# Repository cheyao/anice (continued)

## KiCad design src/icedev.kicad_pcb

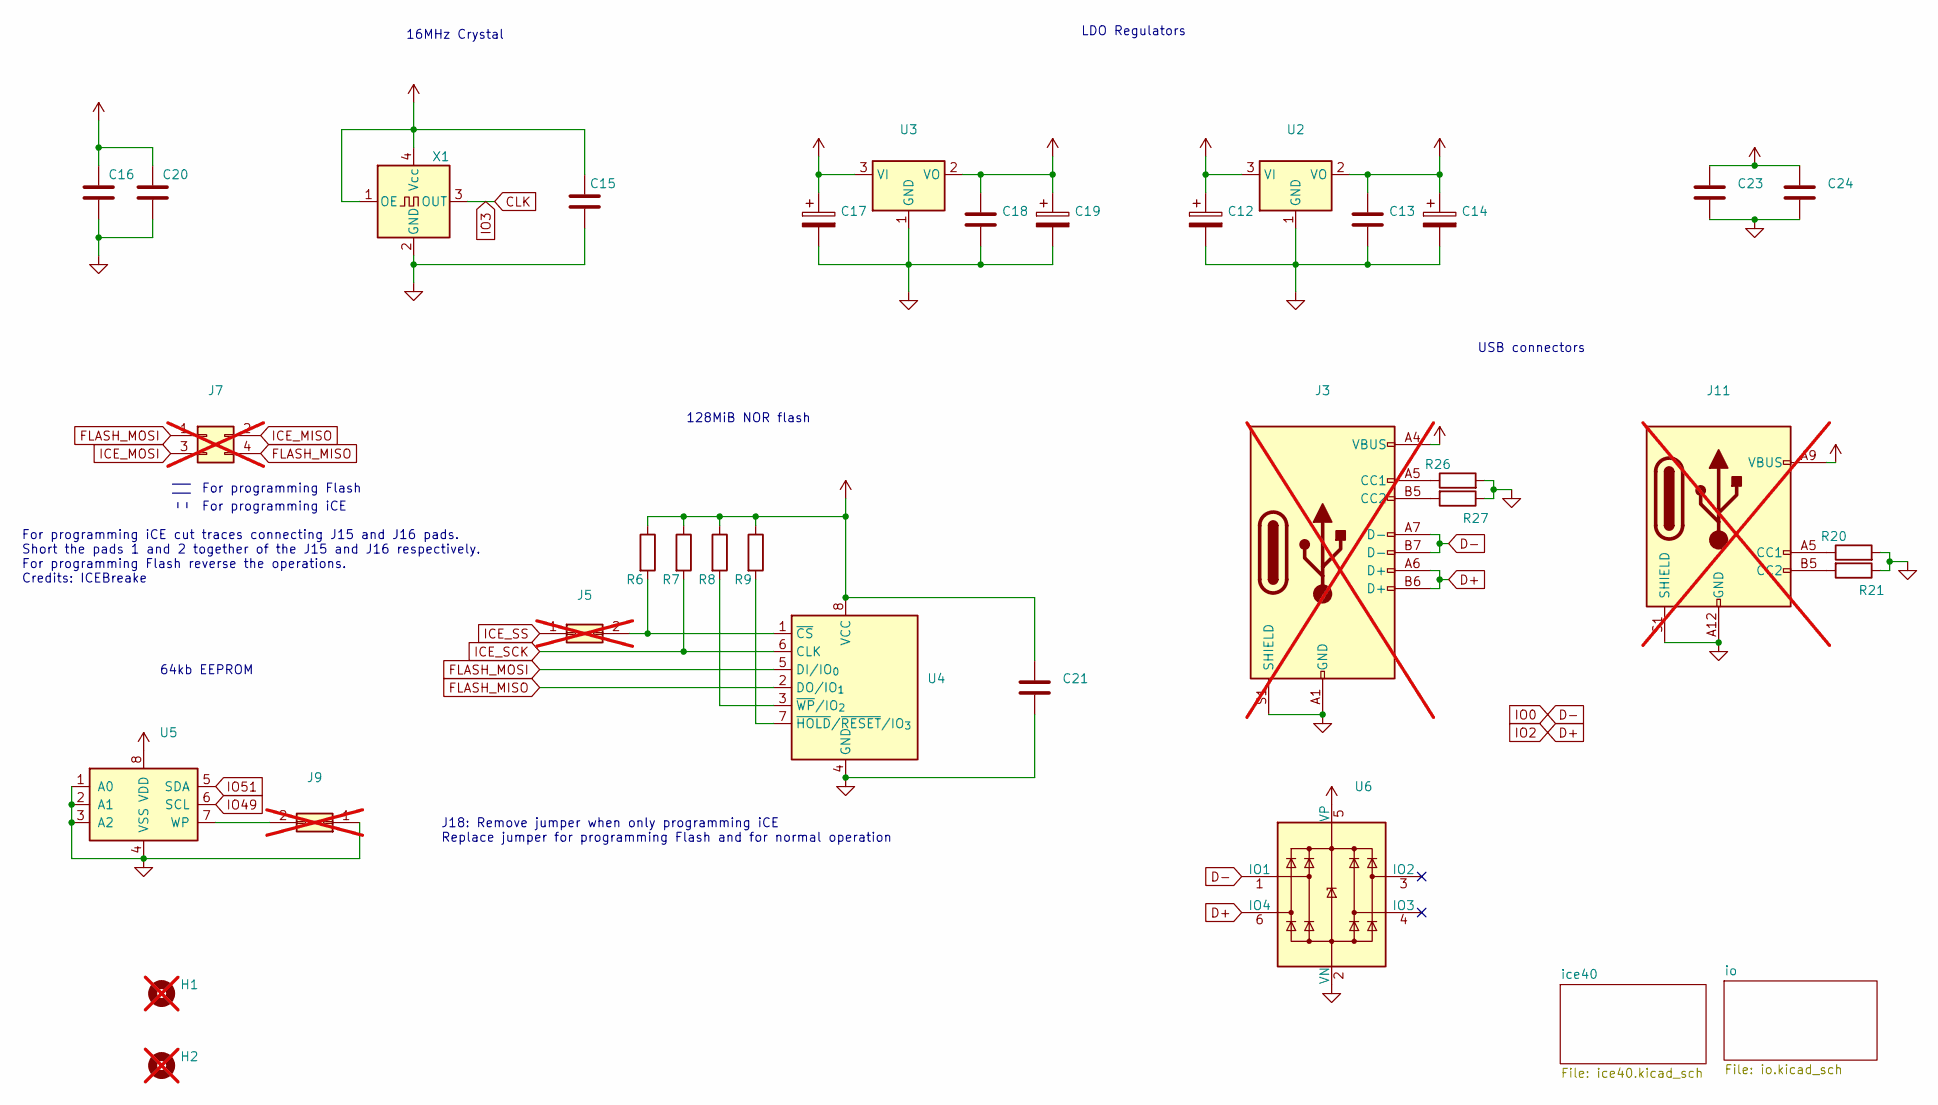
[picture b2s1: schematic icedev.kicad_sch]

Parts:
C12, C14, C17, C19: 10u; C_0402_1005Metric; JLCPCB Part # C15525
C13, C15, C16, C18, C21, C23, C24: 0.1u; C_0402_1005Metric; JLCPCB Part # C1525
C20: 10n; C_0402_1005Metric; JLCPCB Part # C15195
H1, H2: MountingHole; MountingHole_2.2mm_M2; not fitted
J3: USB_C_Receptacle_USB2.0_14P; USB_C_Receptacle_GCT_USB4105-xx-A_16P_TopMnt_Horizontal; not fitted
J5, J9: Conn_02x01; PinHeader_2x01_P2.54mm_Vertical; not fitted
J7: Conn_02x02_Odd_Even; PinSocket_2x02_P2.54mm_Vertical; not fitted
J11: USB_C_Receptacle_PowerOnly_6P; USB_C_Receptacle_GCT_USB4135-GF-A_6P_TopMnt_Horizontal; not fitted
R6, R7, R8, R9: 10K; R_0805_2012Metric; JLCPCB Part # C17414
R20, R21: 5.1K; R_0402_1005Metric; JLCPCB Part # C25905
R26, R27: 5.1K; R_0805_2012Metric; JLCPCB Part # C27834
U2: AMS1117-1.2; SOT-223-3_TabPin2; JLCPCB Part # C14529
U3: AMS1117-3.3; SOT-223-3_TabPin2; JLCPCB Part # C6186
U4: W25Q128JVS; SOIC-8_5.3x5.3mm_P1.27mm; JLCPCB Part # C97521
U5: FM24C64B; SOIC-8_3.9x4.9mm_P1.27mm; JLCPCB Part # C79988
U6: SRV05-4; SOT-23-6-routable; JLCPCB Part # C85364
X1: MPUOSC; Oscillator_SMD_Abracon_ASE-4Pin_3.2x2.5mm; JLCPCB Part # C13738

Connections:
+1V2: C13.1, C14.1, C16.1, C20.1, U2.2 (VO); also elsewhere on the board
+3V3: C12.1, C15.1, C18.1, C19.1, C21.1, R6.1, R7.1, R8.1, R9.1, U2.3 (VI), U3.2 (VO), U4.8 (VCC), U5.8 (VDD), X1.1 (OE), X1.4 (Vcc); also elsewhere on the board
+5V: C17.1, C23.1, C24.1, J3.A4 (VBUS), J3.A9 (VBUS), J3.B4 (VBUS), J3.B9 (VBUS), J11.A9 (VBUS), J11.B9 (VBUS), U3.3 (VI), U6.5 (VP); also elsewhere on the board
CLK: X1.3 (OUT); also elsewhere on the board
D+: J3.A6 (D+), J3.B6 (D+), U6.6 (IO4); also elsewhere on the board
D-: J3.A7 (D-), J3.B7 (D-), U6.1 (IO1); also elsewhere on the board
FLASH_MISO: J7.4, U4.2 (DO/IO_{1}); also elsewhere on the board
FLASH_MOSI: J7.1, U4.5 (DI/IO_{0}); also elsewhere on the board
GND: C12.2, C13.2, C14.2, C15.2, C16.2, C17.2, C18.2, C19.2, C20.2, C21.2, C23.2, C24.2, J3.A1 (GND), J3.A12 (GND), J3.B1 (GND), J3.B12 (GND), J3.S1 (SHIELD), J9.1, J11.A12 (GND), J11.B12 (GND), J11.S1 (SHIELD), R20.2, R21.1, R26.2, R27.1, U2.1 (GND), U3.1 (GND), U4.4 (GND), U5.1 (A0), U5.2 (A1), U5.3 (A2), U5.4 (VSS), U6.2 (VN), X1.2 (GND); also elsewhere on the board
ICE_MISO: J7.2; also elsewhere on the board
ICE_MOSI: J7.3; also elsewhere on the board
ICE_SCK: R7.2, U4.6 (CLK); also elsewhere on the board
ICE_SS: J5.1; also elsewhere on the board
IO49: U5.6 (SCL); also elsewhere on the board
IO51: U5.5 (SDA); also elsewhere on the board
unnamed: J3.A5 (CC1), R26.1
unnamed: J3.B5 (CC2), R27.2
unnamed: J5.2, R6.2, U4.1 (~CS)
unnamed: J9.2, U5.7 (WP)
unnamed: J11.A5 (CC1), R20.1
unnamed: J11.B5 (CC2), R21.2
unnamed: R9.2, U4.7 (~HOLD/~RESET/IO_{3})
unnamed: R8.2, U4.3 (~WP/IO_{2})

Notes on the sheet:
For programming Flash
J18: Remove jumper when only programming iCE Replace jumper for programming Flash and for normal operation
64kb EEPROM
16MHz Crystal
USB connectors
For programming iCE cut traces connecting J15 and J16 pads. Short the pads 1 and 2 together of the J15 and J16 respectively. For programming Flash reverse the operations. Credits: ICEBreake
128MiB NOR flash
LDO Regulators
For programming iCE

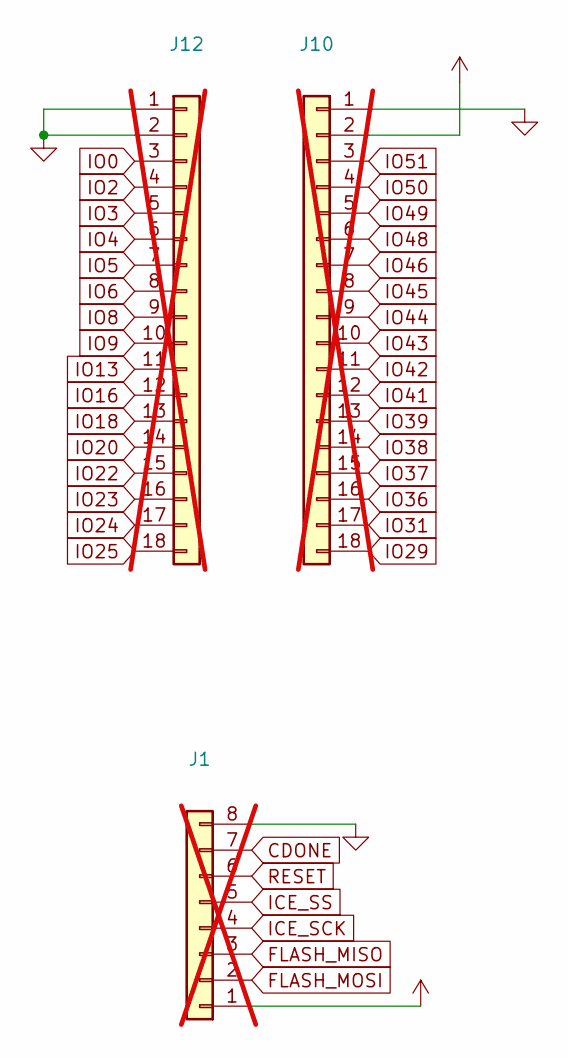
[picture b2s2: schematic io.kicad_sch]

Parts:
J1: Conn_01x08; PinSocket_1x08_P2.54mm_Vertical; not fitted
J10, J12: Conn_01x18; PinSocket_1x18_P2.54mm_Vertical; not fitted

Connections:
+5V: J1.1, J10.2; also elsewhere on the board
CDONE: J1.7; also elsewhere on the board
CLK: J12.5; also elsewhere on the board
D+: J12.4; also elsewhere on the board
D-: J12.3; also elsewhere on the board
FLASH_MISO: J1.3; also elsewhere on the board
FLASH_MOSI: J1.2; also elsewhere on the board
GND: J1.8, J10.1, J12.1, J12.2; also elsewhere on the board
ICE_SCK: J1.4; also elsewhere on the board
ICE_SS: J1.5; also elsewhere on the board
IO4: J12.6; also elsewhere on the board
IO5: J12.7; also elsewhere on the board
IO6: J12.8; also elsewhere on the board
IO8: J12.9; also elsewhere on the board
IO9: J12.10; also elsewhere on the board
IO13: J12.11; also elsewhere on the board
IO16: J12.12; also elsewhere on the board
IO18: J12.13; also elsewhere on the board
IO20: J12.14; also elsewhere on the board
IO22: J12.15; also elsewhere on the board
IO23: J12.16; also elsewhere on the board
IO24: J12.17; also elsewhere on the board
IO25: J12.18; also elsewhere on the board
IO29: J10.18; also elsewhere on the board
IO31: J10.17; also elsewhere on the board
IO36: J10.16; also elsewhere on the board
IO37: J10.15; also elsewhere on the board
IO38: J10.14; also elsewhere on the board
IO39: J10.13; also elsewhere on the board
IO41: J10.12; also elsewhere on the board
IO42: J10.11; also elsewhere on the board
IO43: J10.10; also elsewhere on the board
IO44: J10.9; also elsewhere on the board
IO45: J10.8; also elsewhere on the board
IO46: J10.7; also elsewhere on the board
IO48: J10.6; also elsewhere on the board
IO49: J10.5; also elsewhere on the board
IO50: J10.4; also elsewhere on the board
IO51: J10.3; also elsewhere on the board
RESET: J1.6; also elsewhere on the board

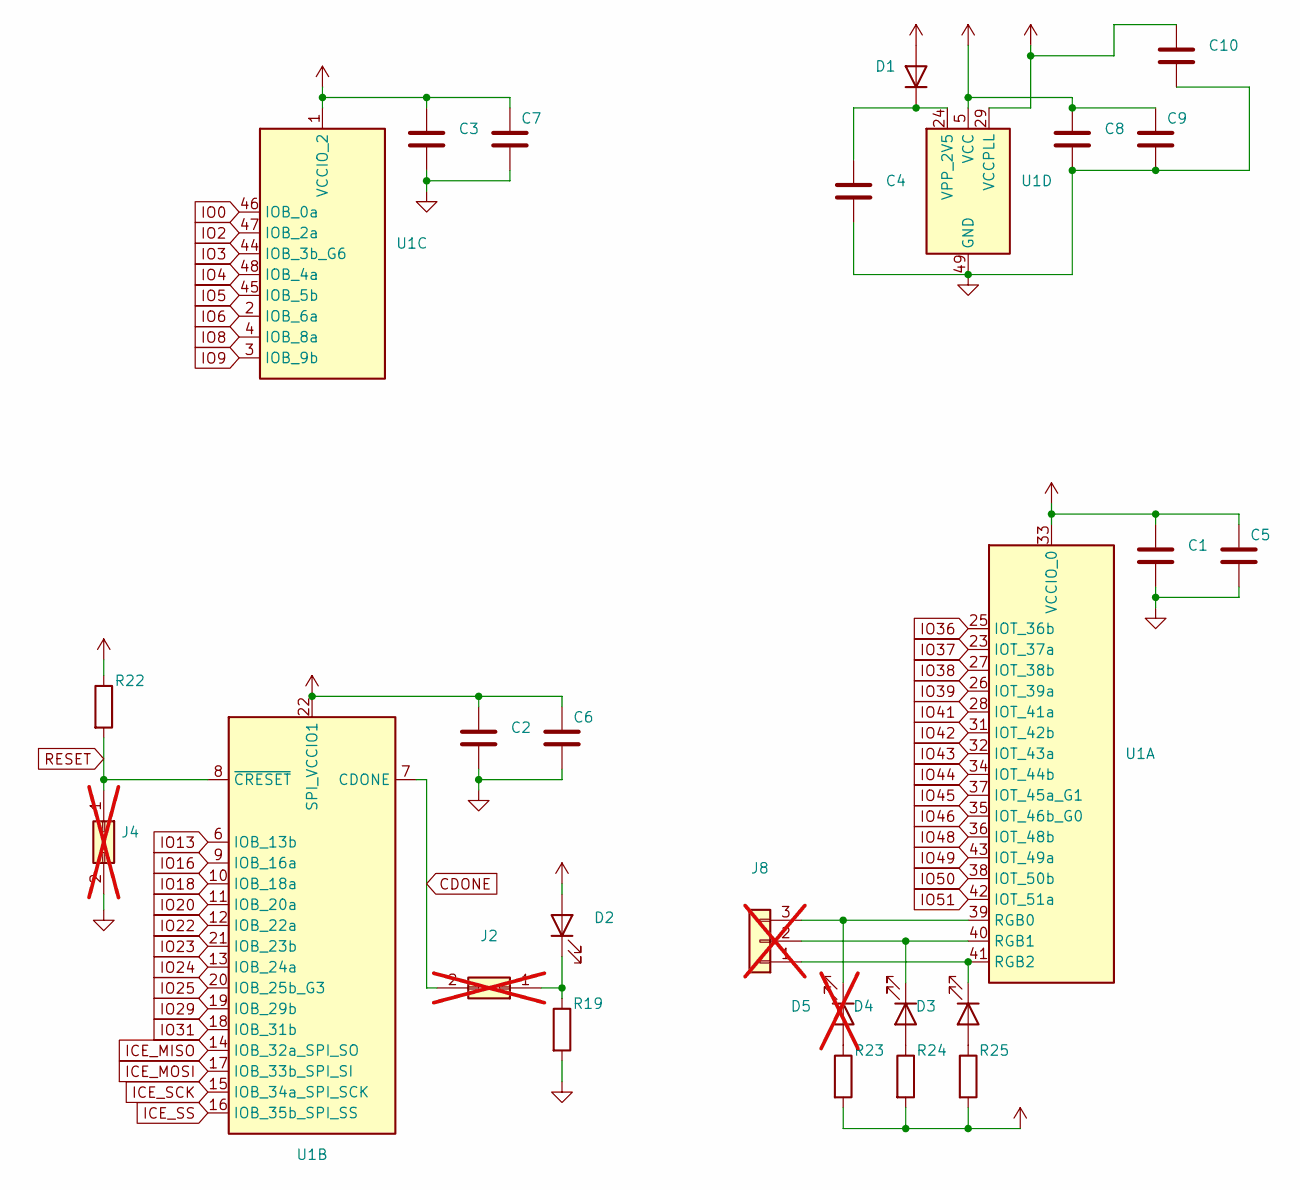
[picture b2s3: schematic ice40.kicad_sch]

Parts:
C1, C2, C3, C4, C8, C10: 0.1u; C_0402_1005Metric; JLCPCB Part # C1525
C5, C6, C7, C9: 10n; C_0402_1005Metric; JLCPCB Part # C15195
D1: Schottky Diode; D_SOD-123; JLCPCB Part # C8598
D2, D4: G; LED_0805_2012Metric; JLCPCB Part # C2297
D3: R; LED_0603_1608Metric; JLCPCB Part # C2286
D5: B; LED_0201_0603Metric_Pad0.64x0.40mm_HandSolder; not fitted
J2, J4: Conn_02x01; PinHeader_2x01_P2.54mm_Vertical; not fitted
J8: Conn_01x03; PinHeader_1x03_P2.54mm_Vertical; not fitted
R19, R22, R23, R24, R25: 1K; R_0805_2012Metric; JLCPCB Part # C17513
U1: ICE40UP5K-SG48ITR; QFN-48-1EP_7x7mm_P0.5mm_EP5.6x5.6mm; JLCPCB Part # C2678152

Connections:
+1V2: C8.1, C9.1, C10.1, U1.5 (VCC), U1.29 (VCCPLL), U1.30 (VCC); also elsewhere on the board
+3V3: C1.1, C2.1, C3.1, C5.1, C6.1, C7.1, D1.2 (A), D2.2 (A), R22.1, R23.2, R24.2, R25.2, U1.1 (VCCIO_2), U1.22 (SPI_VCCIO1), U1.33 (VCCIO_0); also elsewhere on the board
CDONE: J2.2, U1.7 (CDONE); also elsewhere on the board
CLK: U1.44 (IOB_3b_G6); also elsewhere on the board
D+: U1.47 (IOB_2a); also elsewhere on the board
D-: U1.46 (IOB_0a); also elsewhere on the board
GND: C1.2, C2.2, C3.2, C4.2, C5.2, C6.2, C7.2, C8.2, C9.2, C10.2, J4.2, R19.2, U1.49 (GND); also elsewhere on the board
ICE_MISO: U1.14 (IOB_32a_SPI_SO); also elsewhere on the board
ICE_MOSI: U1.17 (IOB_33b_SPI_SI); also elsewhere on the board
ICE_SCK: U1.15 (IOB_34a_SPI_SCK); also elsewhere on the board
ICE_SS: U1.16 (IOB_35b_SPI_SS); also elsewhere on the board
IO4: U1.48 (IOB_4a); also elsewhere on the board
IO5: U1.45 (IOB_5b); also elsewhere on the board
IO6: U1.2 (IOB_6a); also elsewhere on the board
IO8: U1.4 (IOB_8a); also elsewhere on the board
IO9: U1.3 (IOB_9b); also elsewhere on the board
IO13: U1.6 (IOB_13b); also elsewhere on the board
IO16: U1.9 (IOB_16a); also elsewhere on the board
IO18: U1.10 (IOB_18a); also elsewhere on the board
IO20: U1.11 (IOB_20a); also elsewhere on the board
IO22: U1.12 (IOB_22a); also elsewhere on the board
IO23: U1.21 (IOB_23b); also elsewhere on the board
IO24: U1.13 (IOB_24a); also elsewhere on the board
IO25: U1.20 (IOB_25b_G3); also elsewhere on the board
IO29: U1.19 (IOB_29b); also elsewhere on the board
IO31: U1.18 (IOB_31b); also elsewhere on the board
IO36: U1.25 (IOT_36b); also elsewhere on the board
IO37: U1.23 (IOT_37a); also elsewhere on the board
IO38: U1.27 (IOT_38b); also elsewhere on the board
IO39: U1.26 (IOT_39a); also elsewhere on the board
IO41: U1.28 (IOT_41a); also elsewhere on the board
IO42: U1.31 (IOT_42b); also elsewhere on the board
IO43: U1.32 (IOT_43a); also elsewhere on the board
IO44: U1.34 (IOT_44b); also elsewhere on the board
IO45: U1.37 (IOT_45a_G1); also elsewhere on the board
IO46: U1.35 (IOT_46b_G0); also elsewhere on the board
IO48: U1.36 (IOT_48b); also elsewhere on the board
IO49: U1.43 (IOT_49a); also elsewhere on the board
IO50: U1.38 (IOT_50b); also elsewhere on the board
IO51: U1.42 (IOT_51a); also elsewhere on the board
unnamed: C4.1, D1.1 (K), U1.24 (VPP_2V5)
unnamed: D2.1 (K), J2.1, R19.1
unnamed: D3.2 (A), R25.1
unnamed: D3.1 (K), J8.1, U1.41 (RGB2)
unnamed: D4.2 (A), R24.1
unnamed: D4.1 (K), J8.2, U1.40 (RGB1)
unnamed: D5.2 (A), R23.1
unnamed: D5.1 (K), J8.3, U1.39 (RGB0)
RESET: J4.1, R22.2, U1.8 (~CRESET); also elsewhere on the board

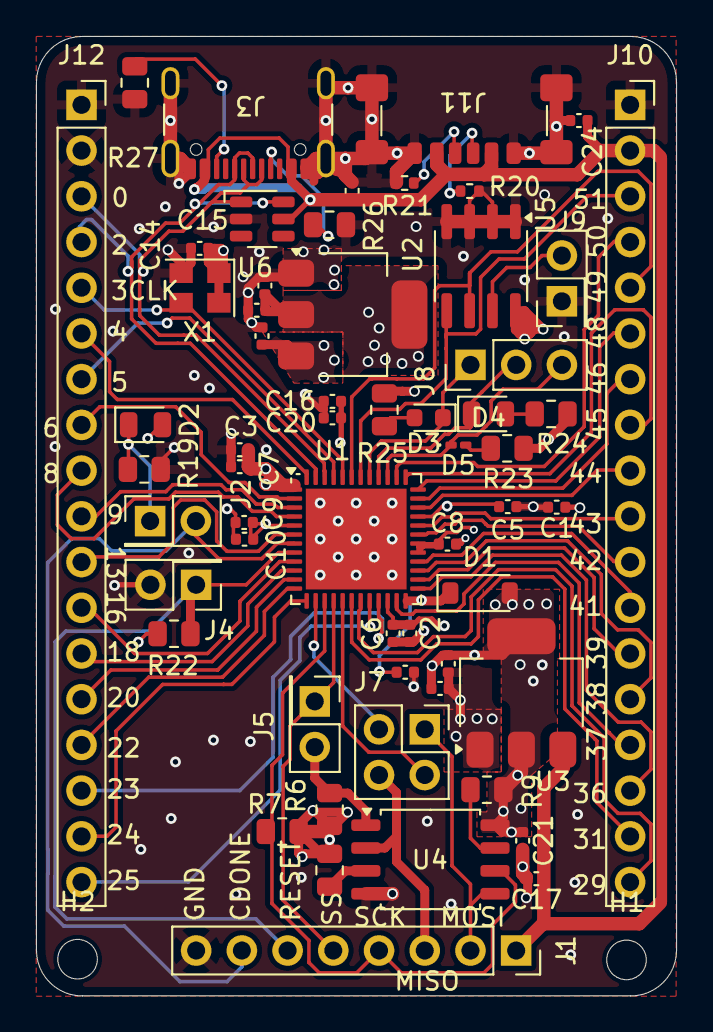
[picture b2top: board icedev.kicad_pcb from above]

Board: 4 copper layers, 35.6 x 53.3 mm, 60 parts (0 on the bottom side), 60 nets.

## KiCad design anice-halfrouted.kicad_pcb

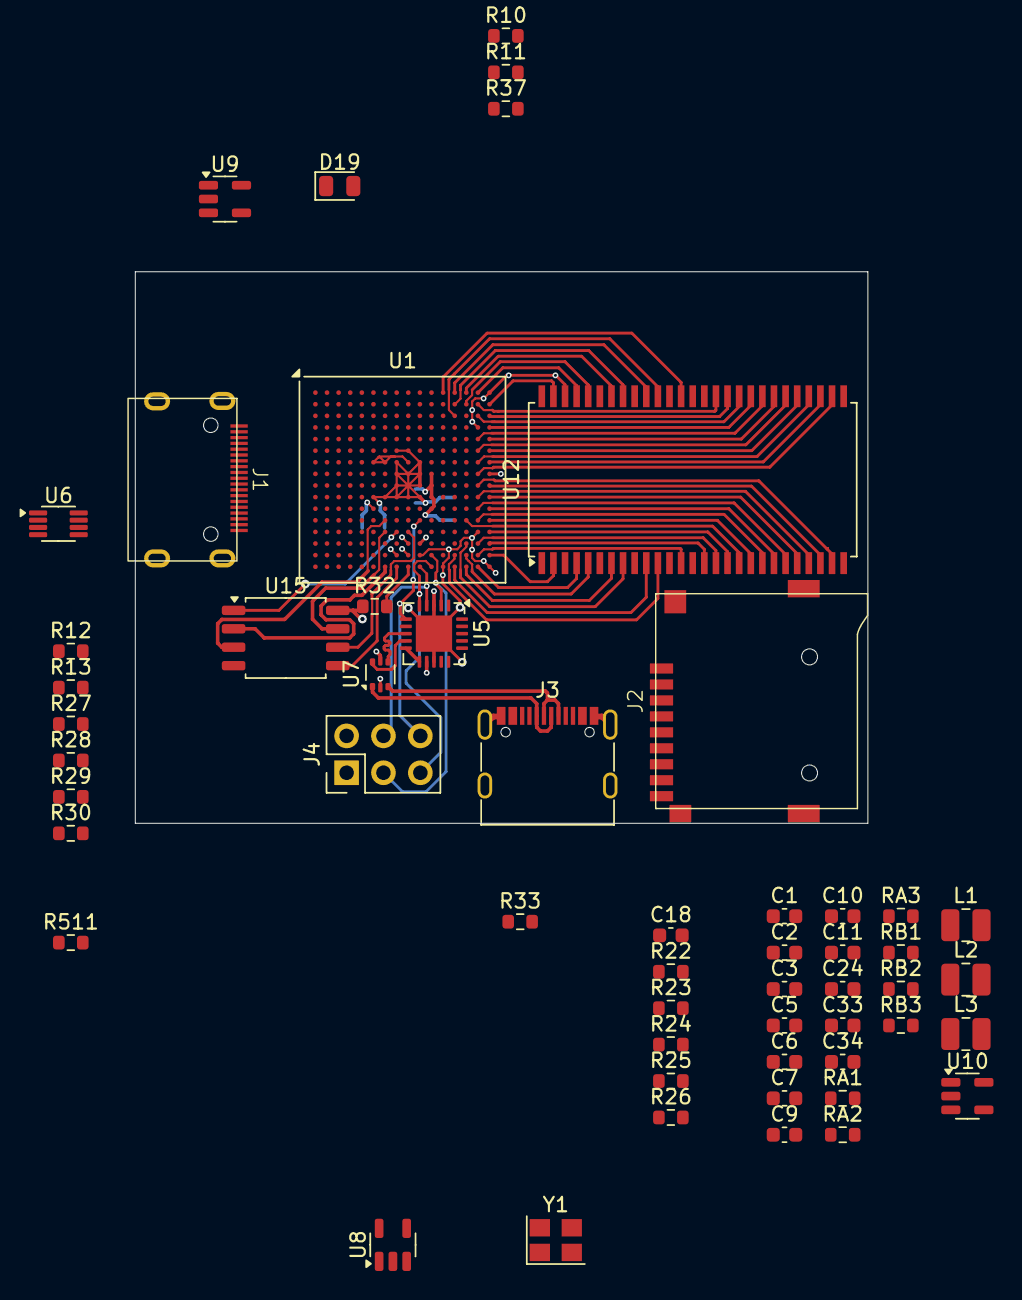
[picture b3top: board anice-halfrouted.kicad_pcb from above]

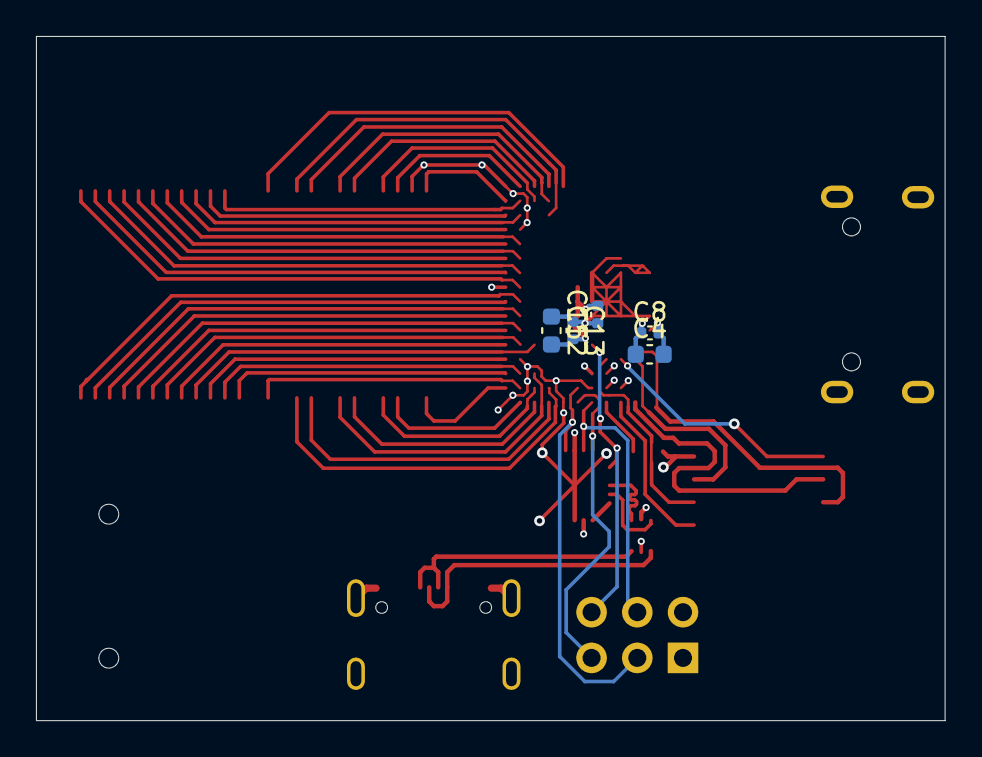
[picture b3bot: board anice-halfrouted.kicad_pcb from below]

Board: 4 copper layers, 50.5 x 38.0 mm, 59 parts (5 on the bottom side), 77 nets.

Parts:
C1, C3, C5, C7, C9, C11: 22uF; C_0603_1608Metric
C2, C4, C12: 10uF; C_0603_1608Metric
C6, C10, C18: 100pF; C_0603_1608Metric
C8, C13, C15: 100nF; C_0402_1005Metric
C24, C33, C34: 2.2uF; C_0603_1608Metric
D19: RED; LED_0805_2012Metric
J1: HDMI_C_1.3; XKB Connection A71-05H4-111N1
J2: Micro_SD_Card_Det1; XYECONN TF-015-ZYD9AH1.85
J3: USB_C_Receptacle_USB2.0_14P; USB_C_Receptacle_G-Switch_GT-USB-7010ASV
J4: CONN_02X03; PinHeader_2x03_P2.54mm_Vertical
L1, L2, L3: 2.2uH; L_1008_2520Metric
R10, R11: 5.1k; R_0603_1608Metric
R12, R13, R27, R28: 10k; R_0603_1608Metric
R22, R23: 3.3k; R_0603_1608Metric
R24: 100k; R_0603_1608Metric
R25, R26, R30, R32, R33, R511: 4.7k; R_0603_1608Metric
R29: 1k; R_0603_1608Metric
R37: 549; R_0603_1608Metric
RA1, RA2, RA3: 15k; R_0603_1608Metric
RB1: 18k; R_0603_1608Metric
RB2: 4.7k; R_0603_1608Metric
RB3: 3.3k; R_0603_1608Metric
U1: ECP5U_12_CABGA256; BGA-256_14.0x14.0mm_Layout16x16_P0.8mm_Ball0.45mm_Pad0.32mm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
U5: FT231XQ; QFN-20-1EP_4x4mm_P0.5mm_EP2.5x2.5mm
U6: PCA9306DC1; VSSOP-8_2.3x2mm_P0.5mm
U7: USBLC6-2P6; SOT-666
U8, U9, U10: TLV62569DBV; SOT-23-5
U12: W9825G6KH-6; TSOP-II-54_22.2x10.16mm_P0.8mm
U15: W25Q128JVS; SOIC-8_5.3x5.3mm_P1.27mm
Y1: ECS-2520MV-xxx-xx; Crystal_SMD_3225-4Pin_3.2x2.5mm

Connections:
+1V1: C2.1, C3.1, C34.1, L1.2, RA1.1, U1.G6 (VCC[6]), U1.G7 (VCC[6]), U1.G9 (VCC[6]), U1.L8 (VCC[6]), U1.L9 (VCC[6]), U1.L10 (VCC[6])
+2V5: C10.1, C11.1, C33.1, L2.2, R22.1, R23.1, RA2.1, U1.G11 (VCCAUX[2]), U1.L7 (VCCAUX[2]), U6.2 (VREF1)
+3V3: C4.2, C6.1, C7.1, C8.2, C12.2, C13.2, C15.2, C24.1, J4.2, L3.2, R12.1, R13.1, R27.1, R28.1, R29.1, R30.1, R32.1, R33.1, R511.1, RA3.1, U1.F6 (VCCIO0[2]), U1.F7 (VCCIO0[2]), U1.F10 (VCCIO1[2]), U1.F11 (VCCIO1[2]), U1.H6 (VCCIO7[2]), U1.H7 (VCCIO7[2]), U1.H11 (VCCIO2[2]), U1.J6 (VCCIO6[2]), U1.J7 (VCCIO6[2]), U1.J11 (VCCIO2[2]), U1.K11 (VCCIO3[2]), U1.L6 (VCCIO8), U1.L11 (VCCIO3[2]), U1.P10 (CFG_1), U1.R8 (PB13A/+/SN/CSN), U6.8 (EN), U12.1 (VDD), U12.3 (VDDQ), U12.9 (VDDQ), U12.14 (VDD), U12.27 (VDD), U12.43 (VDDQ), U12.49 (VDDQ), U15.8 (VCC)
+5V: C1.1, C5.1, C9.1, J1.18 (+5V), J3.A4 (VBUS), J3.A9 (VBUS), J3.B4 (VBUS), J3.B9 (VBUS), R24.1, R25.1, R26.1, U5.12 (VCC), U7.5 (VBUS), U8.1 (EN), U8.4 (VIN), U9.1 (EN), U9.4 (VIN), U10.1 (EN), U10.4 (VIN)
/Power/FB1: C2.2, RA1.2, RB1.2, U8.5 (FB)
/Power/FB2: C10.2, RA2.2, RB2.2, U9.5 (FB)
/Power/FB3: C6.2, RA3.2, RB3.2, U10.5 (FB)
/Power/L1: L1.1, U8.3 (SW)
/Power/L2: L2.1, U9.3 (SW)
/Power/L3: L3.1, U10.3 (SW)
/USB/LED_TXLED: D19.1 (K), R37.2
CLK: R29.2, U1.N9 (CCLK/MCLK/SCK), U15.6 (CLK)
DONE: R33.2, U1.P9 (DONE)
FPDI_SCL: R23.2, U6.3 (SCL1)
FPDI_SDA: R22.2, U6.4 (SDA1)
FT2V5: D19.2 (A), U5.10 (3V3OUT), U5.11 (~RESET), U5.20 (VCCIO)
FTDI_nTXLED: R37.1, U5.7 (CBUS2)
GND: C1.2, C3.2, C4.1, C5.2, C7.2, C8.1, C9.2, C11.2, C12.1, C13.1, C15.1, C18.2, C24.2, C33.2, C34.2, J1.1 (D2S), J1.4 (D1S), J1.7 (D0S), J1.10 (CKS), J1.13 (GND), J1.SH, J3.A1 (GND), J3.A12 (GND), J3.B1 (GND), J3.B12 (GND), J3.S1 (SHIELD), J4.1, R10.1, R11.1, RB1.1, RB2.1, RB3.1, U1.A1 (GND[27]), U1.A16 (GND[27]), U1.D2 (GND[27]), U1.D15 (GND[27]), U1.F8 (GND[27]), U1.F9 (GND[27]), U1.G8 (GND[27]), U1.G10 (GND[27]), U1.H1 (GND[27]), U1.H8 (GND[27]), U1.H9 (GND[27]), U1.H10 (GND[27]), U1.H16 (GND[27]), U1.J8 (GND[27]), U1.J9 (GND[27]), U1.J10 (GND[27]), U1.K6 (GND[27]), U1.K7 (GND[27]), U1.K8 (GND[27]), U1.K9 (GND[27]), U1.K10 (GND[27]), U1.N2 (GND[27]), U1.N10 (CFG_0), U1.N15 (GND[27]), U1.R10 (CFG_2), U1.T1 (GND[27]), U1.T5 (GND[27]), U1.T12 (GND[27]), U1.T16 (GND[27]), U5.3 (GND), U5.13 (GND), U5.21 (GND), U6.1 (GND), U7.2 (GND), U8.2 (GND), U9.2 (GND), U10.2 (GND), U12.6 (VSSQ), U12.12 (VSSQ), U12.28 (VSS), U12.41 (VSS), U12.46 (VSSQ), U12.52 (VSSQ), U12.54 (VSS), U15.4 (GND)
GPDI_SCL: J1.15 (SCL), R25.2, U6.6 (SCL2)
GPDI_SDA: J1.16 (SDA), R26.2, U6.5 (SDA2)
INITN: R32.2, U1.T9 (INITN)
IO0: R28.2, U1.T8 (PB11B/-/D0/MOSI/IO0), U15.5 (DI/IO_{0})
IO1: R27.2, U1.T7 (PB11A/+/D1/MISO/IO1), U15.2 (DO/IO_{1})
IO2: R13.2, U1.M7 (PB9B/-/D2/IO2), U15.3 (~WP/IO_{2})
IO3: R12.2, U1.N7 (PB9A/+/D3/IO3), U15.7 (~HOLD/~RESET/IO_{3})
JTAG_TCK: J4.4, U1.T10 (TCK), U5.4 (~DSR)
JTAG_TDI: J4.3, U1.R11 (TDI), U5.2 (~RI)
JTAG_TDO: J4.6, U1.M10 (TDO), U5.6 (~CTS)
JTAG_TMS: J4.5, U1.T11 (TMS), U5.5 (~DCD)
unnamed: J3.A5 (CC1), R11.2
unnamed: J3.B5 (CC2), R10.2
unnamed: J3.A6 (D+), J3.B6 (D+), U7.3 (IO2)
unnamed: J3.A7 (D-), J3.B7 (D-), U7.1 (IO1)
unnamed: R511.2, U1.R9 (PROGRAMN)
unnamed: U5.9 (USBDM), U7.6 (IO1)
unnamed: U5.8 (USBDP), U7.4 (IO2)
unnamed: C18.1, R24.2, U6.7 (VREF2)
SDRAM_A0: U1.K16 (PR23C/+/PCLKT2_0/RDQ20), U12.23 (A0)
SDRAM_A1: U1.K15 (PR23D/-/PCLKC2_0/RDQ20), U12.24 (A1)
SDRAM_A2: U1.J16 (PR23A/+/PCLKT2_1/HS/RDQ20), U12.25 (A2)
SDRAM_A3: U1.J15 (PR23B/-/PCLKC2_1/HS/RDQ20), U12.26 (A3)
SDRAM_A4: U1.H15 (PR20B/-/HS/RDQSN20), U12.29 (A4)
SDRAM_A5: U1.G16 (PR20A/+/GR_PCLK2_1/HS/RDQS20), U12.30 (A5)
SDRAM_A6: U1.G15 (PR14B/-/HS/RDQ20), U12.31 (A6)
SDRAM_A7: U1.F16 (PR14A/+/HS/RDQ20), U12.32 (A7)
SDRAM_A8: U1.F15 (PR11C/+/RDQ8), U12.33 (A8)
SDRAM_A9: U1.E16 (PR11D/-/RDQ8), U12.34 (A9)
SDRAM_A10: U1.L15 (PR26B/-/PCLKC3_1/HS/RDQ32), U12.22 (A10/AP)
SDRAM_A11: U1.E15 (PR8B/-/HS/RDQSN8), U12.35 (A11)
SDRAM_A12: U1.D16 (PR8A/+/HS/RDQS8), U12.36 (A12)
SDRAM_BA0: U1.M15 (PR26D/-/PCLKC3_0/RDQ32), U12.20 (BS0)
SDRAM_BA1: U1.L16 (PR26A/+/PCLKT3_1/HS/RDQ32), U12.21 (BS1)
SDRAM_CKE: U1.C15 (PR5B/-/HS/RDQ8), U12.37 (CKE)
SDRAM_CLK: U1.C16 (PR5A/+/HS/RDQ8), U12.38 (CLK)
SDRAM_D0: U1.R16 (PR35B/-/VREF1_3/HS/RDQ32), U12.2 (DQ0)
SDRAM_D1: U1.T15 (PR38D/-/RDQ44), U12.4 (DQ1)
SDRAM_D2: U1.R14 (PR41B/-/HS/RDQ44), U12.5 (DQ2)
SDRAM_D3: U1.T14 (PR41D/-/RDQ44), U12.7 (DQ3)
SDRAM_D4: U1.P14 (PR38B/-/HS/RDQ44), U12.8 (DQ4)
SDRAM_D5: U1.T13 (PR44B/-/HS/RDQSN44), U12.10 (DQ5)
SDRAM_D6: U1.R13 (PR41C/+/RDQ44), U12.11 (DQ6)
SDRAM_D7: U1.R15 (PR38C/+/RDQ44), U12.13 (DQ7)
SDRAM_D8: U1.A12 (PT53B/-), U12.42 (DQ8)
SDRAM_D9: U1.C13 (PT60B/-), U12.44 (DQ9)
SDRAM_D10: U1.A13 (PT65A/+), U12.45 (DQ10)
SDRAM_D11: U1.B13 (PT60A/+), U12.47 (DQ11)
SDRAM_D12: U1.A14 (PT65B/-), U12.48 (DQ12)
SDRAM_D13: U1.B14 (PT67A/+), U12.50 (DQ13)
SDRAM_D14: U1.A15 (PT67B/-), U12.51 (DQ14)
SDRAM_D15: U1.B16 (PR2A/+/HS/RDQ8), U12.53 (DQ15)
SDRAM_DQM0: U1.P16 (PR35A/+/HS/RDQ32), U12.15 (LDQM)
SDRAM_DQM1: U1.B15 (PR2B/-/S0_IN/HS/RDQ8), U12.39 (UDQM)
SDRAM_nCAS: U1.N16 (PR32A/+/HS/RDQS32), U12.17 (~CAS)
SDRAM_nCS: U1.M16 (PR26C/+/PCLKT3_0/RDQ32), U12.19 (~CS)
SDRAM_nRAS: U1.M14 (PR32D/-/RDQ32), U12.18 (~RAS)
SDRAM_nWE: U1.P15 (PR32B/-/HS/RDQSN32), U12.16 (~WE)
~CS: R30.2, U1.N8 (PB15A/+/HOLDN/DI/BUSY/CSSPIN/CEN), U15.1 (~CS)

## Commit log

2025-04-22 started routing
2025-04-22 Add a gitignore
2025-04-23 Routed HDMI, usb, rotated chip and more
2025-04-25 Stash
2025-04-25 Add gitignore
2025-04-25 Rev 1
2025-04-25 No DRC Errors
2025-04-25 Structure project
2025-04-25 Clean up repo
2025-04-26 Rev 2
2025-04-26 Tidy project
2025-04-26 Add test points
2025-04-28 Add annotations
2025-04-28 Fix date
2025-04-28 Update LICENSE
